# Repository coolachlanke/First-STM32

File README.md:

# My First STM32 Project

Simple PCB with minimum circuit plus SWD, USART, I2C and USB. Designed wholly in KiCAD 9.

---
Take a look a the fully sick 3D render:

---
..and now take a look at the fully sick assembled board:

The board's indicator LEDs are both on. The green 'PWR' LED indicates the 3V3 bus is live. The orange 'DEBUG' LED is a result of the 'blinky' routine being in the HIGH state.

---
The following HAL-free c script is used to blink the DEBUG LED by writing directly to memory-mapped peripheral registers.

```#include <stdint.h>

int main(void) {
    // Enable GPIOC clock
    volatile uint32_t *rcc_apb2enr = (volatile uint32_t *)0x40021018;
    *rcc_apb2enr |= (1 << 4); // Set IOPCEN (bit 4)

    // Configure PC13 as output push-pull, 10 MHz
    volatile uint32_t *gpioc_crh = (volatile uint32_t *)0x40011004;
    *gpioc_crh &= ~(0xF << 20); // Clear MODE13 and CNF13
    *gpioc_crh |= (0x1 << 20); // MODE13 = 01 (output 10 MHz), CNF13 = 00 (push-pull)

    // DR Register
    volatile uint32_t *gpioc_odr = (volatile uint32_t *)0x4001100C;

    // SysTick Registers
    volatile uint32_t *systick_ctrl = (volatile uint32_t *)0xE000E010;
    volatile uint32_t *systick_load = (volatile uint32_t *)0xE000E014;
    volatile uint32_t *systick_val  = (volatile uint32_t *)0xE000E018;

    // SysTick Init
    *systick_load = (8000000 / 1000) - 1;  // Reload for 1ms tick
    *systick_val  = 0;                     // Clear current value
    *systick_ctrl = (1 << 2) | (1 << 0);   // CLKSOURCE=CPU, ENABLE=1

    // Delay Function
    void delay_ms(uint32_t ms) {
        for (uint32_t i = 0; i < ms; ++i) {
            while (((*systick_ctrl) & (1 << 16)) == 0);
        }
    }

    // Main Blink Loop
    while (1) {
        *gpioc_odr &= ~(1 << 13);  // Set PC13 LOW
        delay_ms(250);

        *gpioc_odr |= (1 << 13);   // Set PC13 HIGH
        delay_ms(250);
    }
}

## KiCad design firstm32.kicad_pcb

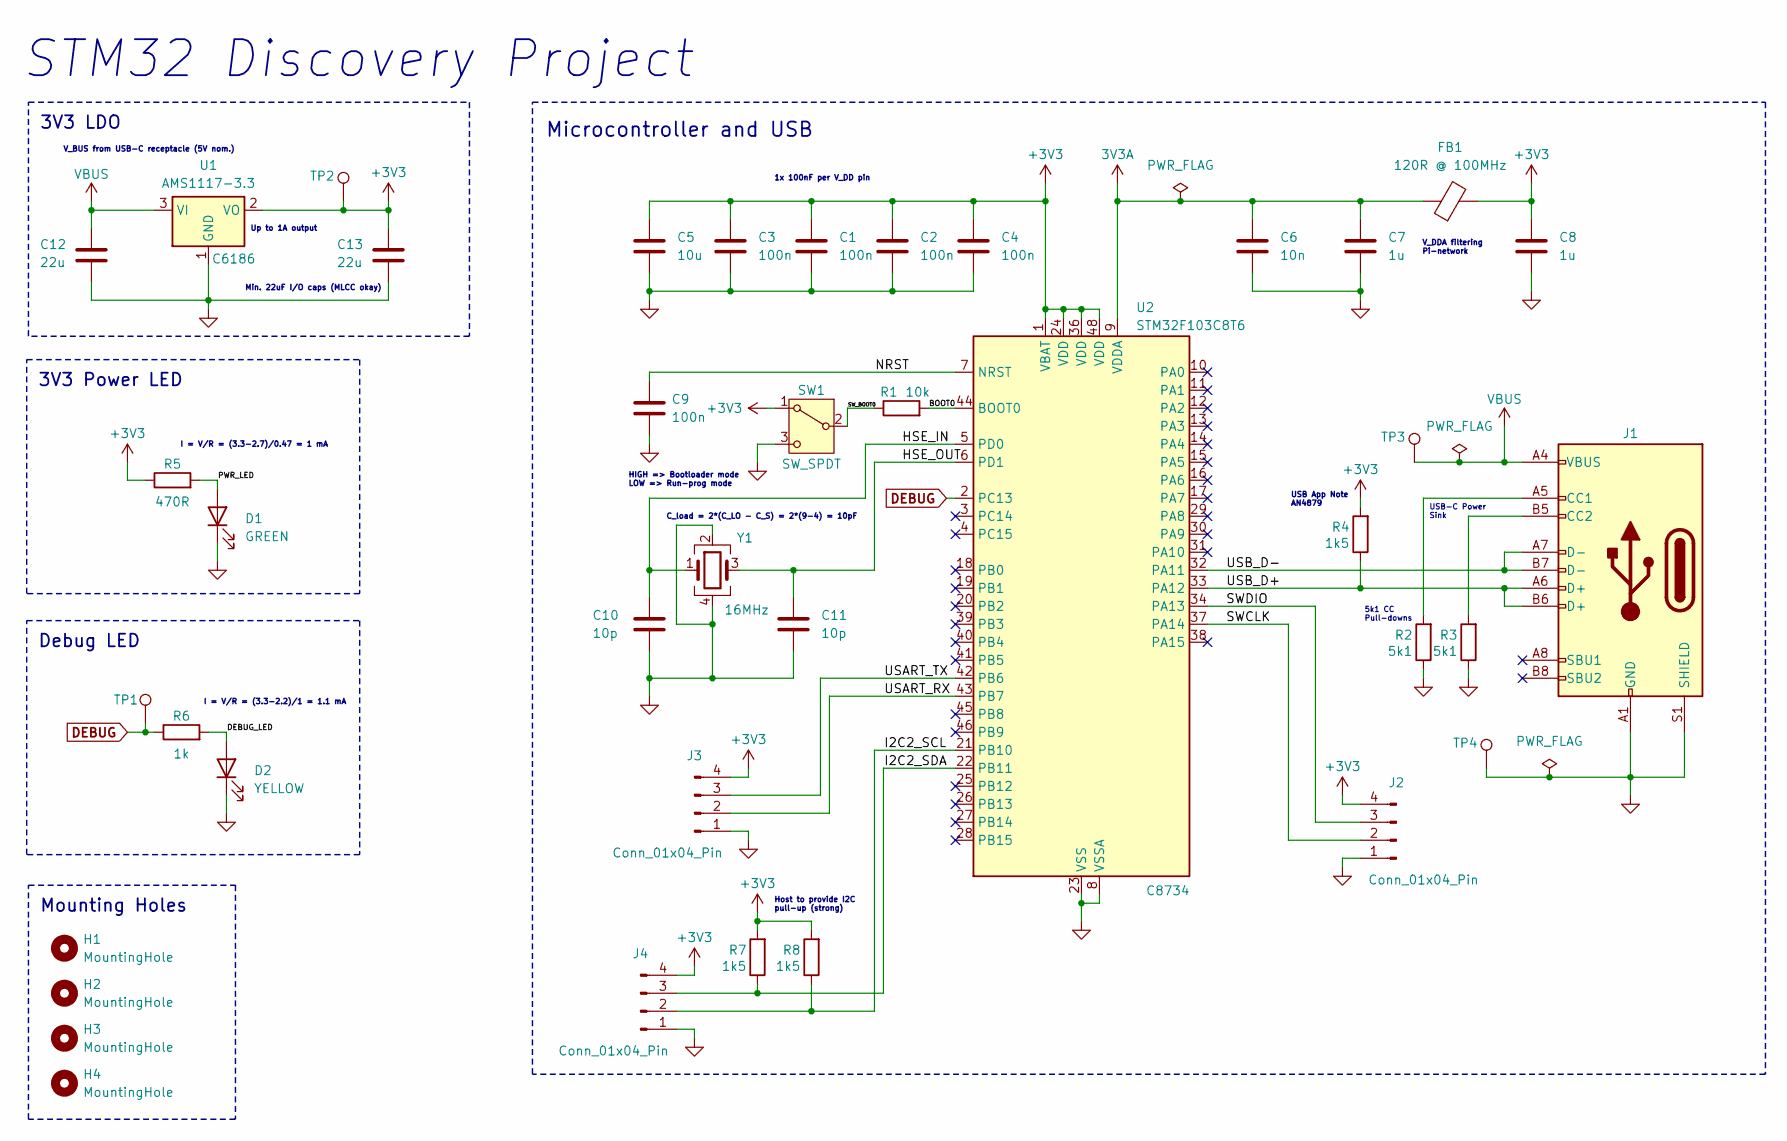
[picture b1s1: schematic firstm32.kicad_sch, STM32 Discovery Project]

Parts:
C1, C2, C3, C4, C9: 100n; C_0402_1005Metric; LCSC C1525
C5: 10u; C_0603_1608Metric; LCSC C19702
C6: 10n; C_0402_1005Metric; LCSC C15195
C7, C8: 1u; C_0603_1608Metric; LCSC C15849
C10, C11: 10p; C_0402_1005Metric; LCSC C32949
C12, C13: 22u; C_0805_2012Metric; LCSC C45783
D1: GREEN; LED_0805_2012Metric; LCSC C2297
D2: YELLOW; LED_0805_2012Metric; LCSC C2296
FB1: 120R @ 100MHz; L_0603_1608Metric; LCSC C14709
H1, H2, H3, H4: MountingHole; MountingHole_2.2mm_M2
J1: USB_C_Receptacle_USB2.0_16P; USB-C-SMD_TYPE-C-6PIN-2MD-073; LCSC C2765186
J2, J3, J4: Conn_01x04_Pin; HDR-TH_4P-P2.54-V-M; LCSC C2691448
R1: 10k; C_0402_1005Metric; LCSC C25744
R2, R3: 5k1; R_0402_1005Metric; LCSC C25905
R4, R7, R8: 1k5; R_0402_1005Metric; LCSC C25867
R5: 470R; R_0603_1608Metric; LCSC C23179
R6: 1k; R_0603_1608Metric; LCSC C21190
SW1: SW_SPDT; SW-SMD_K3-1280S-K1; LCSC C92658
TP1, TP2, TP3, TP4: TestPoint; TestPoint_THTPad_D1.5mm_Drill0.7mm
U1: AMS1117-3.3; SOT-223-3_TabPin2; LCSC C6186
U2: STM32F103C8T6; LQFP-48_7x7mm_P0.5mm; LCSC C8734
Y1: 16MHz; OSC-SMD_4P-L3.2-W2.5-BL; LCSC C13738

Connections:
3V3A: C6.1, C7.1, FB1.1, U2.9 (VDDA)
+3V3: C1.1, C2.1, C3.1, C4.1, C5.1, C8.1, C13.1, FB1.2, J2.4, J3.4, J4.4, R4.2, R5.1, R7.2, R8.2, SW1.1 (A), TP2.1, U1.2 (VO), U2.1 (VBAT), U2.24 (VDD), U2.36 (VDD), U2.48 (VDD)
/BOOT0: R1.2, U2.44 (BOOT0)
/DEBUG_LED: D2.2 (A), R6.2
/HSE_IN: C10.1, U2.5 (PD0), Y1.1
/HSE_OUT: C11.1, U2.6 (PD1), Y1.3
/I2C2_SCL: J4.2, R8.1, U2.21 (PB10)
/I2C2_SDA: J4.3, R7.1, U2.22 (PB11)
/NRST: C9.1, U2.7 (NRST)
/PWR_LED: D1.2 (A), R5.2
/SWCLK: J2.2, U2.37 (PA14)
/SWDIO: J2.3, U2.34 (PA13)
/SW_BOOT0: R1.1, SW1.2 (B)
/USART_RX: J3.2, U2.43 (PB7)
/USART_TX: J3.3, U2.42 (PB6)
/USB_D+: J1.A6 (D+), J1.B6 (D+), R4.1, U2.33 (PA12)
/USB_D-: J1.A7 (D-), J1.B7 (D-), U2.32 (PA11)
DEBUG: R6.1, TP1.1, U2.2 (PC13)
GND: C1.2, C2.2, C3.2, C4.2, C5.2, C6.2, C7.2, C8.2, C9.2, C10.2, C11.2, C12.2, C13.2, D1.1 (K), D2.1 (K), J1.A1 (GND), J1.A12 (GND), J1.B1 (GND), J1.B12 (GND), J1.S1 (SHIELD), J2.1, J3.1, J4.1, R2.1, R3.1, SW1.3 (C), TP4.1, U1.1 (GND), U2.8 (VSSA), U2.23 (VSS), U2.35 (VSS), U2.47 (VSS), Y1.2, Y1.4
unnamed: J1.A5 (CC1), R2.2
unnamed: J1.B5 (CC2), R3.2
VBUS: C12.1, J1.A4 (VBUS), J1.A9 (VBUS), J1.B4 (VBUS), J1.B9 (VBUS), TP3.1, U1.3 (VI)

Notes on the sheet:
I = V/R = (3.3-2.7)/0.47 = 1 mA
Up to 1A output
Debug LED
HIGH => Bootloader mode LOW => Run-prog mode
5k1 CC Pull-downs
Min. 22uF I/O caps (MLCC okay)
C_load = 2*(C_LO - C_S) = 2*(9-4) = 10pF
V_DDA filtering Pi-network
V_BUS from USB-C receptacle (5V nom.)
USB-C Power Sink
USB App Note AN4879
1x 100nF per V_DD pin
Host to provide I2C pull-up (strong)
3V3 Power LED
Mounting Holes
I = V/R = (3.3-2.2)/1 = 1.1 mA
STM32 Discovery Project
Microcontroller and USB
3V3 LDO

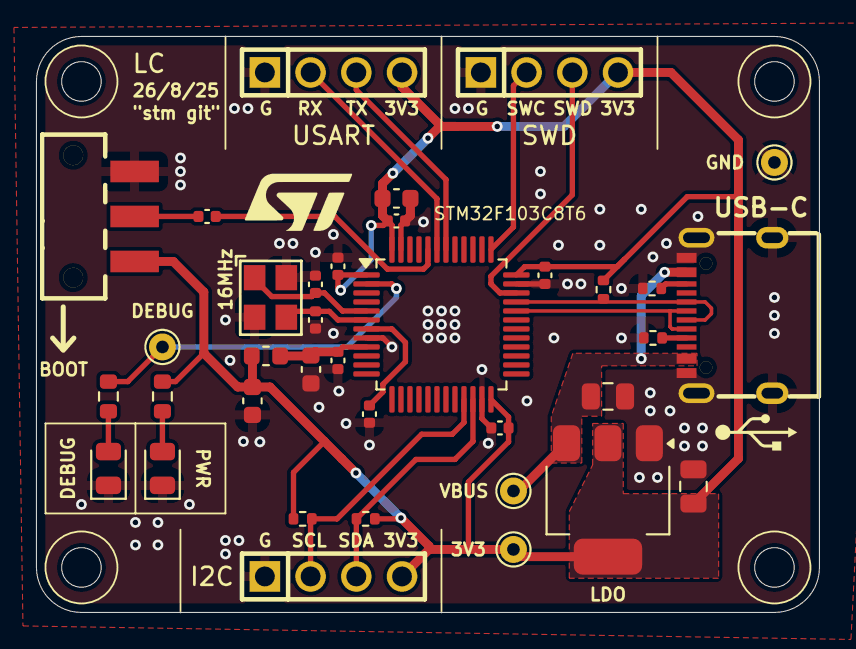
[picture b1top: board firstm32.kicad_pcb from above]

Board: 2 copper layers, 43.5 x 32.0 mm, 40 parts (0 on the bottom side), 22 nets.

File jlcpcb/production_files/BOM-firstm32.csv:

Comment,Designator,Footprint,LCSC,Quantity
16MHz,Y1,OSC-SMD_4P-L3.2-W2.5-BL,C13738,1
120R @ 100MHz,FB1,L_0603_1608Metric,C14709,1
10n,C6,C_0402_1005Metric,C15195,1
100n,"C1,C2,C3,C4,C9",C_0402_1005Metric,C1525,5
1u,"C7,C8",C_0603_1608Metric,C15849,2
10u,C5,C_0603_1608Metric,C19702,1
1k,R6,R_0603_1608Metric,C21190,1
YELLOW,D2,LED_0805_2012Metric,C2296,1
GREEN,D1,LED_0805_2012Metric,C2297,1
470R,R5,R_0603_1608Metric,C23179,1
10k,R1,C_0402_1005Metric,C25744,1
1k5,"R4,R7,R8",R_0402_1005Metric,C25867,3
5k1,"R2,R3",R_0402_1005Metric,C25905,2
Conn_01x04_Pin,"J2,J3,J4",HDR-TH_4P-P2.54-V-M,C2691448,3
USB_C_Receptacle_USB2.0_16P,J1,USB-C-SMD_TYPE-C-6PIN-2MD-073,C2765186,1
10p,"C10,C11",C_0402_1005Metric,C32949,2
22u,"C12,C13",C_0805_2012Metric,C45783,2
AMS1117-3.3,U1,SOT-223-3_TabPin2,C6186,1
STM32F103C8T6,U2,LQFP-48_7x7mm_P0.5mm,C8734,1
SW_SPDT,SW1,SW-SMD_K3-1280S-K1,C92658,1
TestPoint,TP4,TestPoint_THTPad_D1.5mm_Drill0.7mm,,1
TestPoint,TP2,TestPoint_THTPad_D1.5mm_Drill0.7mm,,1
TestPoint,TP1,TestPoint_THTPad_D1.5mm_Drill0.7mm,,1
TestPoint,TP3,TestPoint_THTPad_D1.5mm_Drill0.7mm,,1

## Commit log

2025-08-26 Initial commit.
2025-08-26 Finished board layout
2025-08-27 Finalised board and ordered with JLCPCC + PCBA
2025-08-27 added render lah
2025-09-02 Added assembled board image
2025-09-03 Resolving conflicts
2025-09-03 Accurate timing using SysTick
2025-09-17 Pulled apart firmware and building/compilation/linking to raw 1s and 0s!
